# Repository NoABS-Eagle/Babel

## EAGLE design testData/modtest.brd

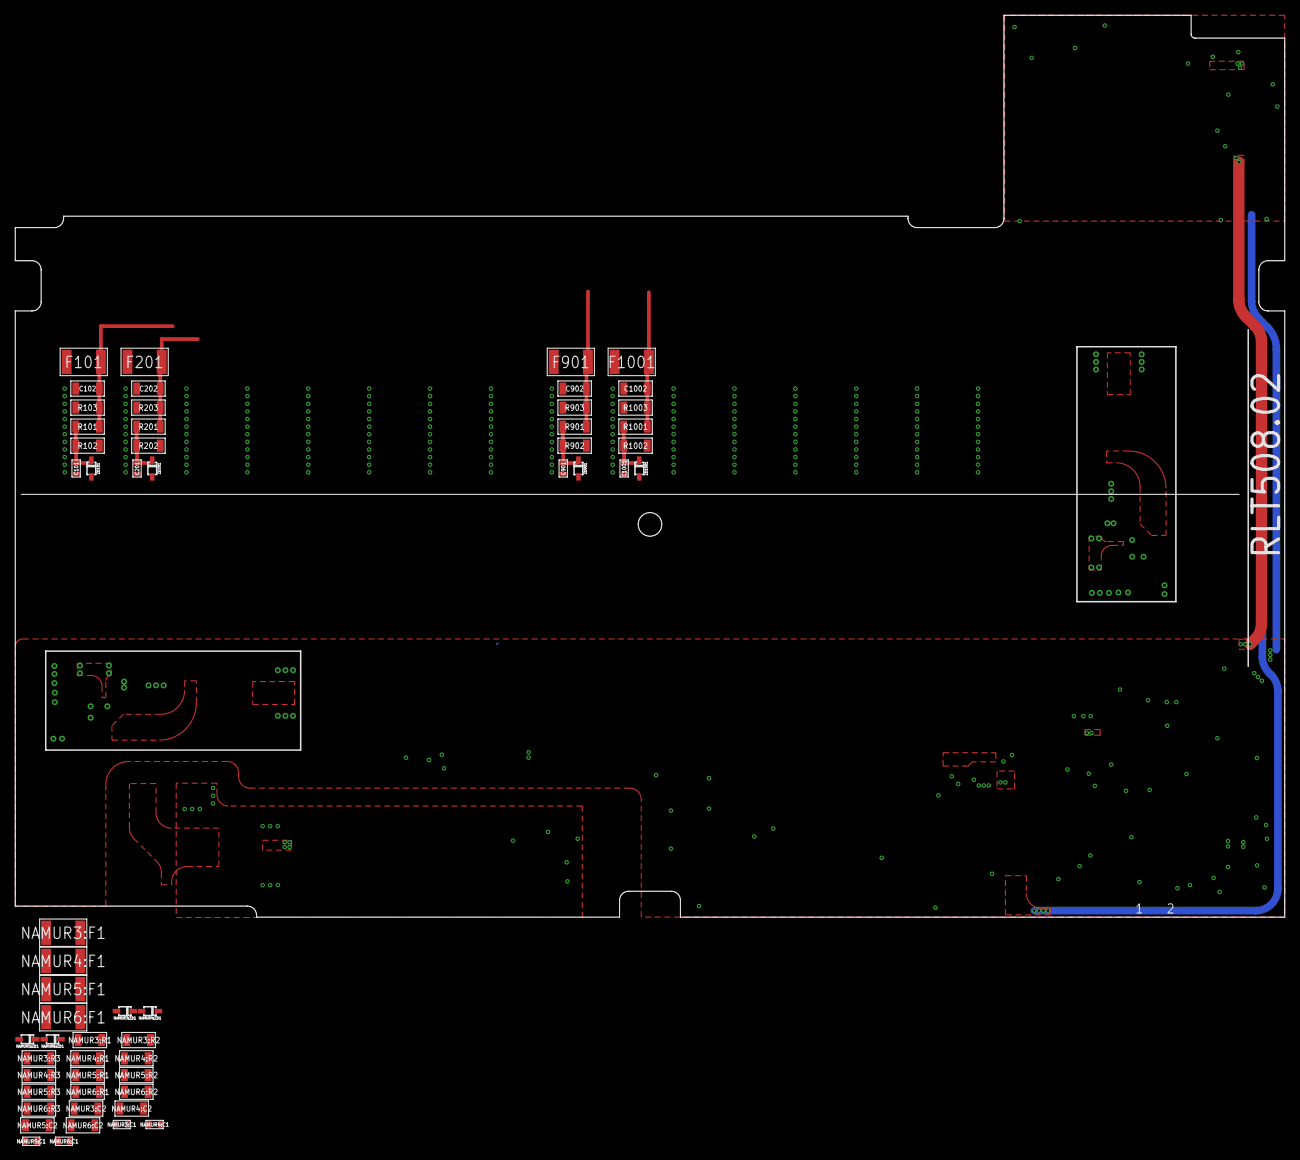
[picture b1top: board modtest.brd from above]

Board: 4 copper layers, 166.8 x 118.5 mm, 56 parts (0 on the bottom side), 10 nets.

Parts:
C101, C201, C901, C1001: 10n; C0603
C102, C202, C902, C1002: 4700p; C1206
F101, F201, F901, F1001: SURGE_ARRESTER-S30-A90X; S30-A90X
NAMUR3:C1, NAMUR4:C1, NAMUR5:C1, NAMUR6:C1: 10n; C0603
NAMUR3:C2, NAMUR4:C2, NAMUR5:C2, NAMUR6:C2: 4700p; C1206
NAMUR3:F1, NAMUR4:F1, NAMUR5:F1, NAMUR6:F1: SURGE_ARRESTER-S30-A90X; S30-A90X
NAMUR3:R1, NAMUR4:R1, NAMUR5:R1, NAMUR6:R1: 47K; R1206
NAMUR3:R2, NAMUR4:R2, NAMUR5:R2, NAMUR6:R2: 33K; R1206
NAMUR3:R3, NAMUR4:R3, NAMUR5:R3, NAMUR6:R3: 1K; R1206
NAMUR3:ZD1, NAMUR4:ZD1, NAMUR5:ZD1, NAMUR6:ZD1: MM3Z3V3; SOD323
R101, R201, R901, R1001: 47K; R1206
R102, R202, R902, R1002: 33K; R1206
R103, R203, R903, R1003: 1K; R1206
ZD101, ZD201, ZD901, ZD1001: MM3Z3V3; SOD323

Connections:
ADC0: C101.2, NAMUR3:C1.2, NAMUR3:R1.P$1, NAMUR3:R2.P$2, NAMUR3:ZD1.C, R101.P$1, R102.P$2, ZD101.C
ADC1: C201.2, NAMUR4:C1.2, NAMUR4:R1.P$1, NAMUR4:R2.P$2, NAMUR4:ZD1.C, R201.P$1, R202.P$2, ZD201.C
ADC8: C901.2, NAMUR5:C1.2, NAMUR5:R1.P$1, NAMUR5:R2.P$2, NAMUR5:ZD1.C, R901.P$1, R902.P$2, ZD901.C
ADC9: C1001.2, NAMUR6:C1.2, NAMUR6:R1.P$1, NAMUR6:R2.P$2, NAMUR6:ZD1.C, R1001.P$1, R1002.P$2, ZD1001.C
GND: C101.1, C102.P$1, C201.1, C202.P$1, C901.1, C902.P$1, C1001.1, C1002.P$1, NAMUR3:C1.1, NAMUR3:C2.P$1, NAMUR3:R2.P$1, NAMUR3:R3.P$1, NAMUR3:ZD1.A, NAMUR4:C1.1, NAMUR4:C2.P$1, NAMUR4:R2.P$1, NAMUR4:R3.P$1, NAMUR4:ZD1.A, NAMUR5:C1.1, NAMUR5:C2.P$1, NAMUR5:R2.P$1, NAMUR5:R3.P$1, NAMUR5:ZD1.A, NAMUR6:C1.1, NAMUR6:C2.P$1, NAMUR6:R2.P$1, NAMUR6:R3.P$1, NAMUR6:ZD1.A, R102.P$1, R103.P$1, R202.P$1, R203.P$1, R902.P$1, R903.P$1, R1002.P$1, R1003.P$1, ZD101.A, ZD201.A, ZD901.A, ZD1001.A
GNDD: F101.2, F201.2, F901.2, F1001.2, NAMUR3:F1.2, NAMUR4:F1.2, NAMUR5:F1.2, NAMUR6:F1.2
NAMUR0: C102.P$2, F101.1, NAMUR3:C2.P$2, NAMUR3:F1.1, NAMUR3:R1.P$2, NAMUR3:R3.P$2, R101.P$2, R103.P$2
NAMUR1: C202.P$2, F201.1, NAMUR4:C2.P$2, NAMUR4:F1.1, NAMUR4:R1.P$2, NAMUR4:R3.P$2, R201.P$2, R203.P$2
NAMUR8: C902.P$2, F901.1, NAMUR5:C2.P$2, NAMUR5:F1.1, NAMUR5:R1.P$2, NAMUR5:R3.P$2, R901.P$2, R903.P$2
NAMUR9: C1002.P$2, F1001.1, NAMUR6:C2.P$2, NAMUR6:F1.1, NAMUR6:R1.P$2, NAMUR6:R3.P$2, R1001.P$2, R1003.P$2

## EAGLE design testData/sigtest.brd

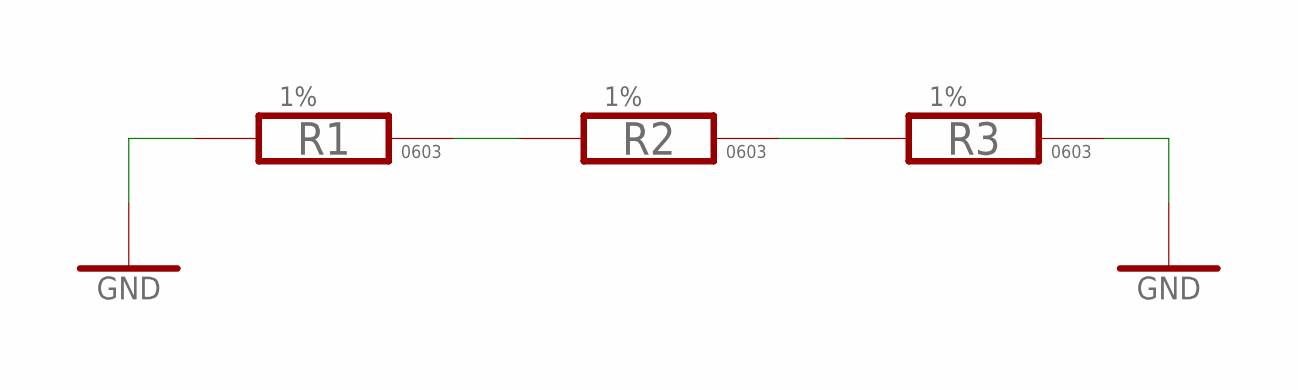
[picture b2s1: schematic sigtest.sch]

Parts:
R1, R2, R3: R-1%-0603; R0603

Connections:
GND: R1.2, R3.1
unnamed: R1.1, R2.2
unnamed: R2.1, R3.2

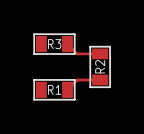
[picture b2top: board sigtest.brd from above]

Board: 2 copper layers, 3 parts (0 on the bottom side), 3 nets.

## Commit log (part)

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2026-06-20 Add Babel converter: Eagle/Altium/KiCad <-> IR pipeline
    First commit of the actual project code (babel/ package was never
    tracked before). Includes Eagle<->IR, Altium<->IR, IR->KiCad converters,
    SVG renderer, Flask viewer app, design docs, and test fixtures.
    Adds .gitignore for runtime session cache, CDN-downloaded 3D viewer
    assets, a third-party installer binary, generated exporter output,
    and Eagle's own editor backup files - none of which belong in version
